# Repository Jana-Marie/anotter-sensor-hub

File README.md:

# anotter-sensor-hub

This is an ESP32-based environmental sensor hub that comes with a Prometheus interface. It is designed to work perfectly with Sensirion SEN05x sensors, such as the depictured SEN055. These sensors provide PM1, PM2.5, PM4, PM10, temperature, humidity, VOC, and NOC indices. In addition, other I2C, SPI, or PWM sensors can be added to the designated connectors. All ESP32 pins are broken out, allowing you to connect any sensor imaginable to the host board.

The PCB and components (w/o SEN055) are about ~5$, with SEN055 it comes up to ~40€/sensor node. 

<table>
  <tbody>
    <tr>
      <td>
        
      </td>
      <td>
        
      </td>
    </tr>
    <tr>
      <td colspan="2">
        
      </td>
    </tr>
  </tbody>
</table>

## Notes

 - Cable: [JST GHR 6Pin to Molex PicoBlade 6Pin](https://www.ebay.de/itm/183753208063)
 - Sensor: [SEN055](https://www.mouser.de/ProductDetail/Sensirion/SEN55-SDN-T)
 - 3D-Print: [4x foot](https://github.com/Jana-Marie/anotter-sensor-hub/blob/main/mechanical/anotter-sensor-hub-foot.stl)

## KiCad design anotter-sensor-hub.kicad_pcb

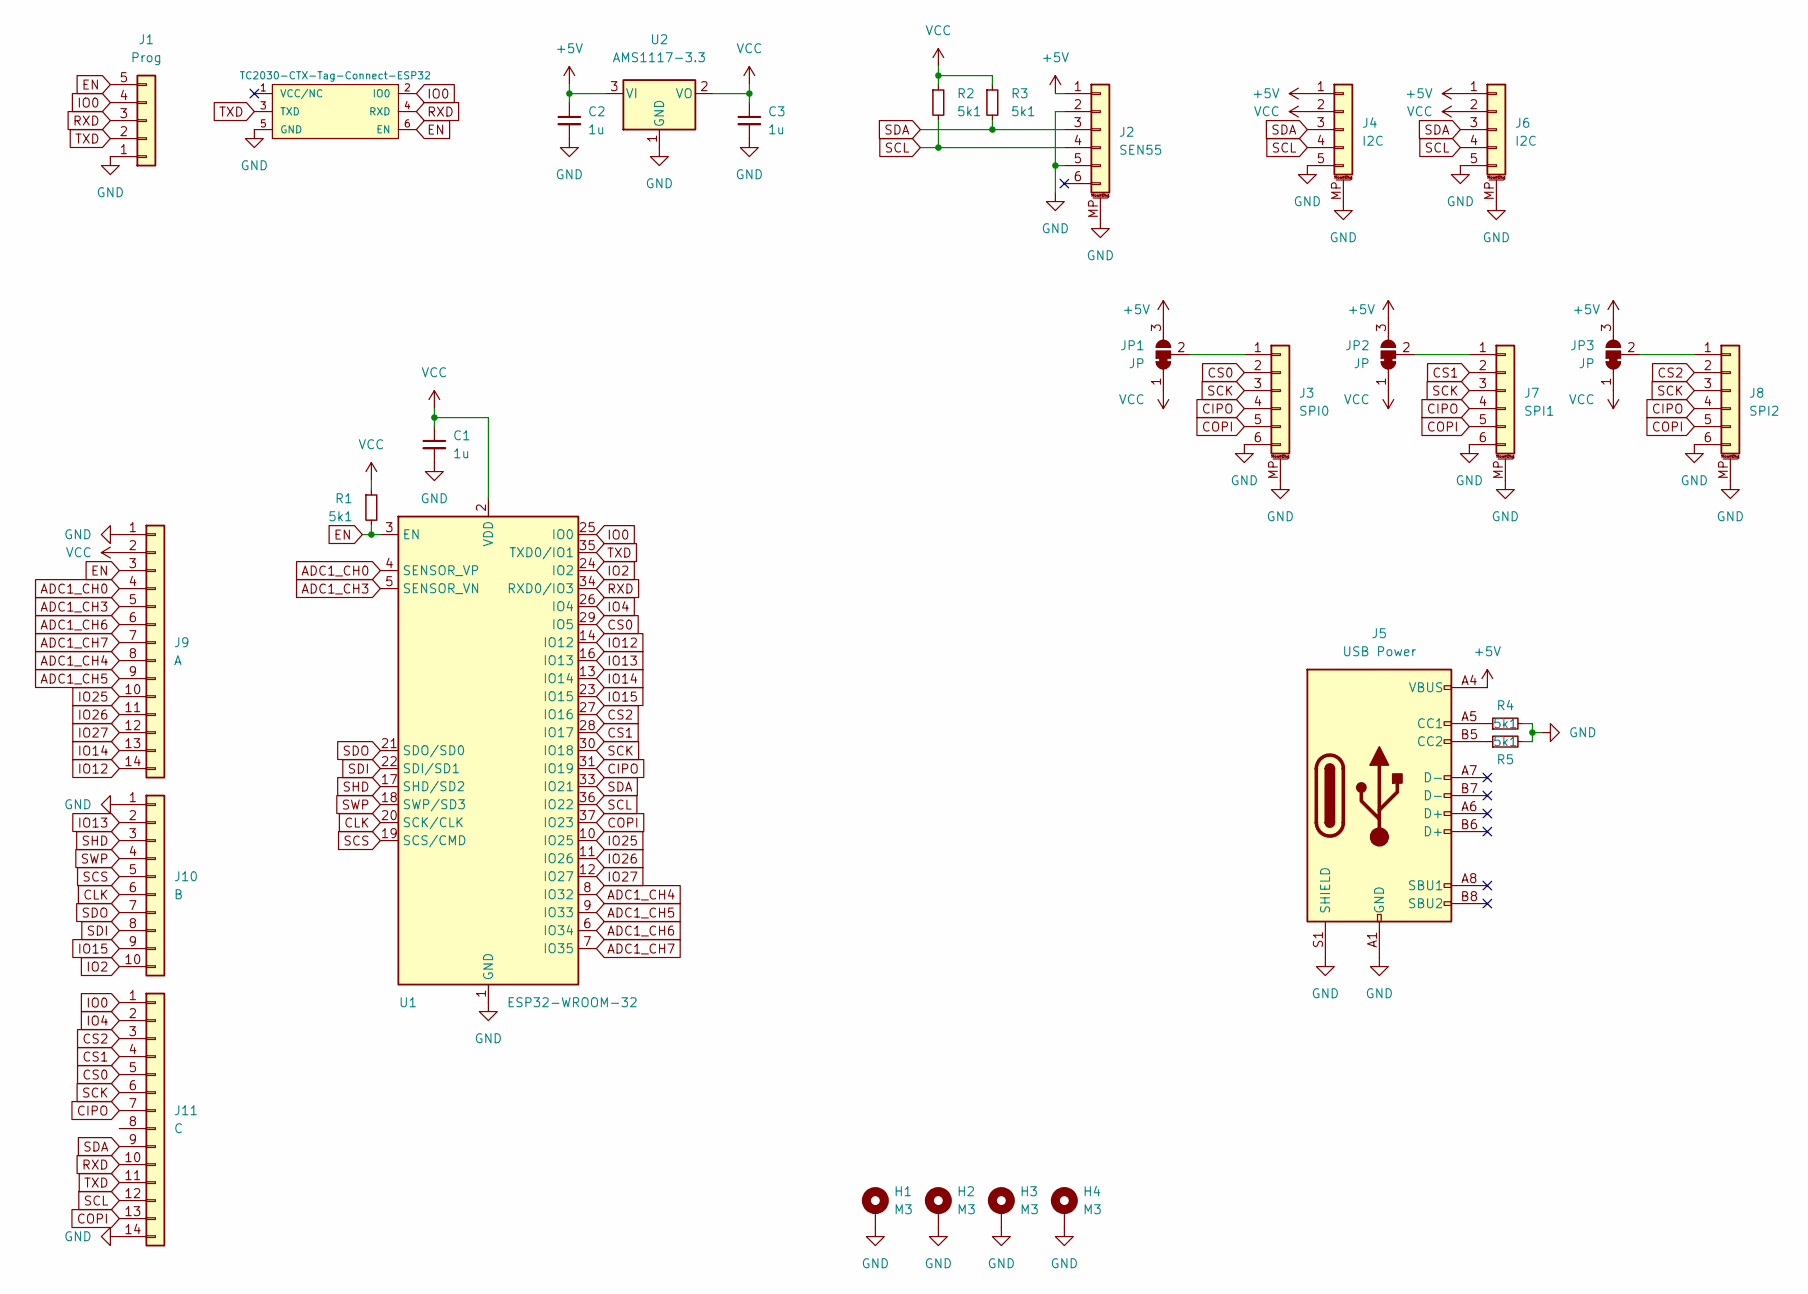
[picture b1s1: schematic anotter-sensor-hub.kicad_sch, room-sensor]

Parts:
C1, C2, C3: 1u; C_0805
H1, H2, H3, H4: M3; MountingHole_3.2mm_M3_Pad_Via
J1: Prog; PinHeader_1x05_P2.54mm_Vertical
J2: SEN55; Molex_PicoBlade_53261-0671_1x06-1MP_P1.25mm_Horizontal
J3: SPI0; Molex_PicoBlade_53261-0671_1x06-1MP_P1.25mm_Horizontal
J4, J6: I2C; Molex_PicoBlade_53398-0571_1x05-1MP_P1.25mm_Vertical
J5: USB Power; USB-C 16Pin
J7: SPI1; Molex_PicoBlade_53398-0671_1x06-1MP_P1.25mm_Vertical
J8: SPI2; Molex_PicoBlade_53398-0671_1x06-1MP_P1.25mm_Vertical
J9: A; PinHeader_1x14_P1.27mm_Vertical
J10: B; PinHeader_1x10_P1.27mm_Vertical
J11: C; PinHeader_1x14_P1.27mm_Vertical
JP1, JP2, JP3: JP; J_0603_90
P1: TC2030-CTX-Tag-Connect-ESP32; TC2030
R1, R2, R3, R4, R5: 5k1; R_0603
U1: ESP32-WROOM-32
U2: AMS1117-3.3; SOT-223-3_TabPin2

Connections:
+5V: C2.1, J2.1, J4.1, J5.A4 (VBUS), J5.A9 (VBUS), J5.B4 (VBUS), J5.B9 (VBUS), J6.1, JP1.3 (B), JP2.3 (B), JP3.3 (B), U2.3 (VI)
ADC1_CH0: J9.4, U1.4 (SENSOR_VP)
ADC1_CH3: J9.5, U1.5 (SENSOR_VN)
ADC1_CH4: J9.8, U1.8 (IO32)
ADC1_CH5: J9.9, U1.9 (IO33)
ADC1_CH6: J9.6, U1.6 (IO34)
ADC1_CH7: J9.7, U1.7 (IO35)
CIPO: J3.4, J7.4, J8.4, J11.7, U1.31 (IO19)
CLK: J10.6, U1.20 (SCK/CLK)
COPI: J3.5, J7.5, J8.5, J11.13, U1.37 (IO23)
CS0: J3.2, J11.5, U1.29 (IO5)
CS1: J7.2, J11.4, U1.28 (IO17)
CS2: J8.2, J11.3, U1.27 (IO16)
EN: J1.5, J9.3, P1.6 (EN), R1.2, U1.3 (EN)
GND: C1.2, C2.2, C3.2, H1.1, H2.1, H3.1, H4.1, J1.1, J2.2, J2.5, J2.MP (MountPin), J3.6, J3.MP (MountPin), J4.5, J4.MP (MountPin), J5.A1 (GND), J5.A12 (GND), J5.B1 (GND), J5.B12 (GND), J5.S1 (SHIELD), J6.5, J6.MP (MountPin), J7.6, J7.MP (MountPin), J8.6, J8.MP (MountPin), J9.1, J10.1, J11.14, P1.5 (GND), R4.2, R5.2, U1.1 (GND), U1.15 (GND), U1.38 (GND), U1.39 (GND), U2.1 (GND)
IO0: J1.4, J11.1, P1.2 (IO0), U1.25 (IO0)
IO2: J10.10, U1.24 (IO2)
IO4: J11.2, U1.26 (IO4)
IO12: J9.14, U1.14 (IO12)
IO13: J10.2, U1.16 (IO13)
IO14: J9.13, U1.13 (IO14)
IO15: J10.9, U1.23 (IO15)
IO25: J9.10, U1.10 (IO25)
IO26: J9.11, U1.11 (IO26)
IO27: J9.12, U1.12 (IO27)
unnamed: J5.A5 (CC1), R4.1
unnamed: J5.B5 (CC2), R5.1
unnamed: J3.1, JP1.2 (C)
unnamed: J7.1, JP2.2 (C)
unnamed: J8.1, JP3.2 (C)
RXD: J1.3, J11.10, P1.4 (RXD), U1.34 (RXD0/IO3)
SCK: J3.3, J7.3, J8.3, J11.6, U1.30 (IO18)
SCL: J2.4, J4.4, J6.4, J11.12, R2.2, U1.36 (IO22)
SCS: J10.5, U1.19 (SCS/CMD)
SDA: J2.3, J4.3, J6.3, J11.9, R3.2, U1.33 (IO21)
SDI: J10.8, U1.22 (SDI/SD1)
SDO: J10.7, U1.21 (SDO/SD0)
SHD: J10.3, U1.17 (SHD/SD2)
SWP: J10.4, U1.18 (SWP/SD3)
TXD: J1.2, J11.11, P1.3 (TXD), U1.35 (TXD0/IO1)
VCC: C1.1, C3.1, J4.2, J6.2, J9.2, JP1.1 (A), JP2.1 (A), JP3.1 (A), R1.1, R2.1, R3.1, U1.2 (VDD), U2.2 (VO)

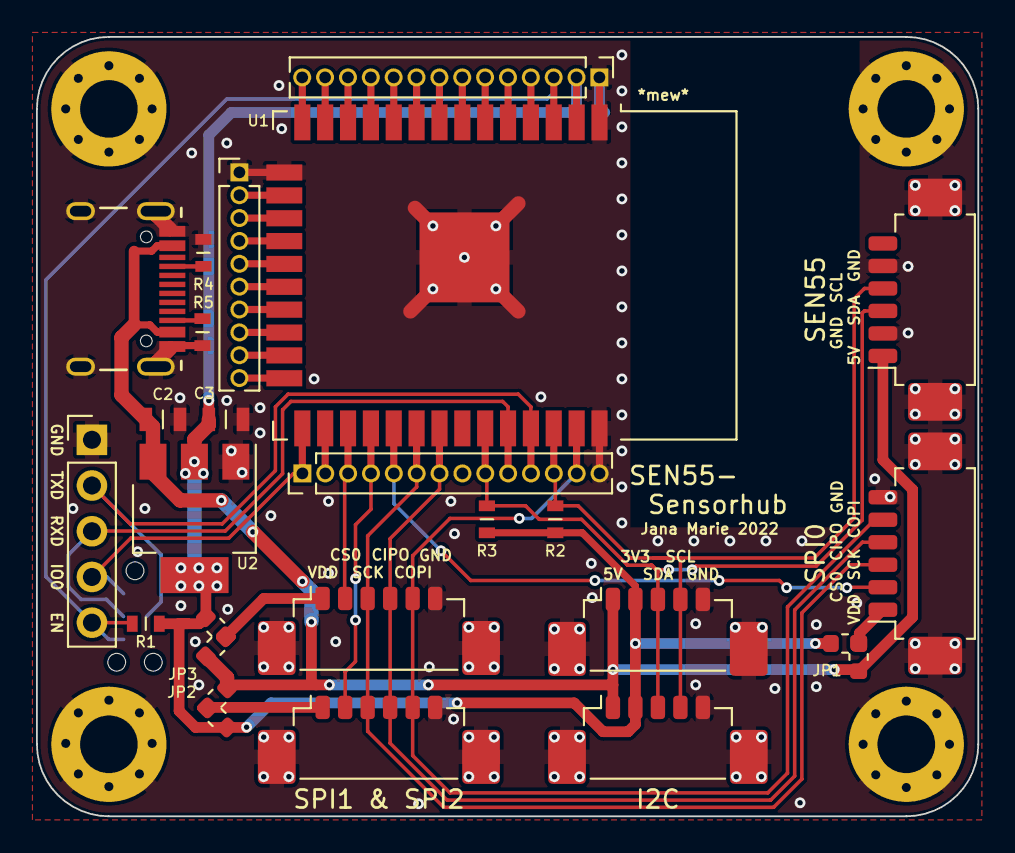
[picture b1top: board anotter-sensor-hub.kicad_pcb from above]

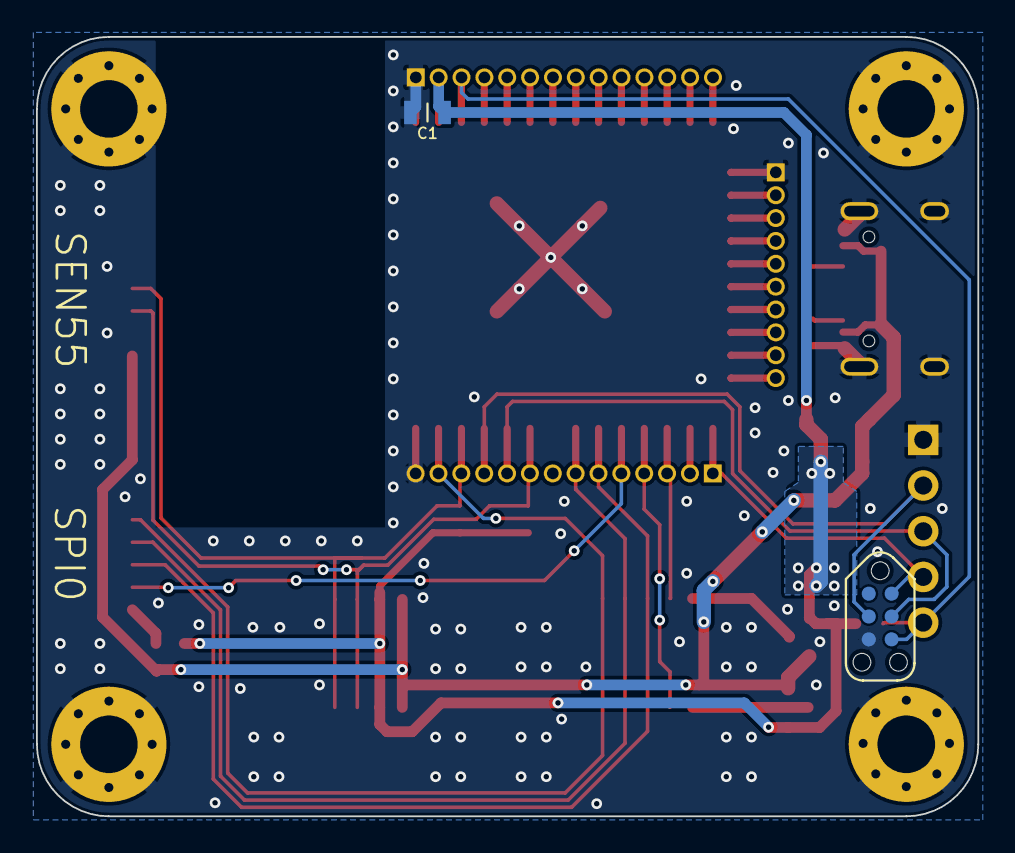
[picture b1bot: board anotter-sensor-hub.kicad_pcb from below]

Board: 2 copper layers, 52.3 x 43.3 mm, 29 parts (2 on the bottom side), 41 nets.

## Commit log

2023-01-29 initial hardware commit
2023-01-29 added gitignore
2023-01-29 update gitignore
2023-01-29 added 3D files
2023-01-29 added fw
2023-01-29 added images
2023-01-29 added grafana dashbaord
2023-01-30 better table
2023-02-28 Create LICENSE
2023-04-14 updated BOM
